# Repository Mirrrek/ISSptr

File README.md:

# ISSptr

A lil thing that points towards the ISS.

## Required hardware

- [The PCB](https://github.com/Mirrrek/ISSptr/tree/main/schematic), obviously, including:
  - [ESP32-WROOM-32-N4](https://jlcpcb.com/partdetail/EspressifSystems-ESP32_WROOM_32N4/C82899) Microcontroller
  - [QMC5883L](https://jlcpcb.com/partdetail/Qst-QMC5883L/C976032) Magnetometer
  - [ULN2003AD](https://jlcpcb.com/partdetail/TexasInstruments-ULN2003AD/C908113) Transistor Array
  - [AMS1117-3.3](https://jlcpcb.com/partdetail/Advanced_MonolithicSystems-AMS1117_33/C6186) Voltage Regulator
  - [BC817](https://jlcpcb.com/partdetail/Shikues-BC817/C475629) NPN Transistors
  - [TYPE-C-31-M-12](https://jlcpcb.com/partdetail/Korean_HropartsElec-TYPE_C_31_M12/C165948) USB-C Connector
  - [B5B-XH-A(LF)(SN)](https://jlcpcb.com/partdetail/Jst-B5B_XH_A_LF_SN/C157991) Connector
  - Some 0603 resistors and capacitors
- A servo motor (e.g. _SG90_)
- An unipolar stepper motor (e.g. _28BYJ-48_)
- 6-Channel slip ring

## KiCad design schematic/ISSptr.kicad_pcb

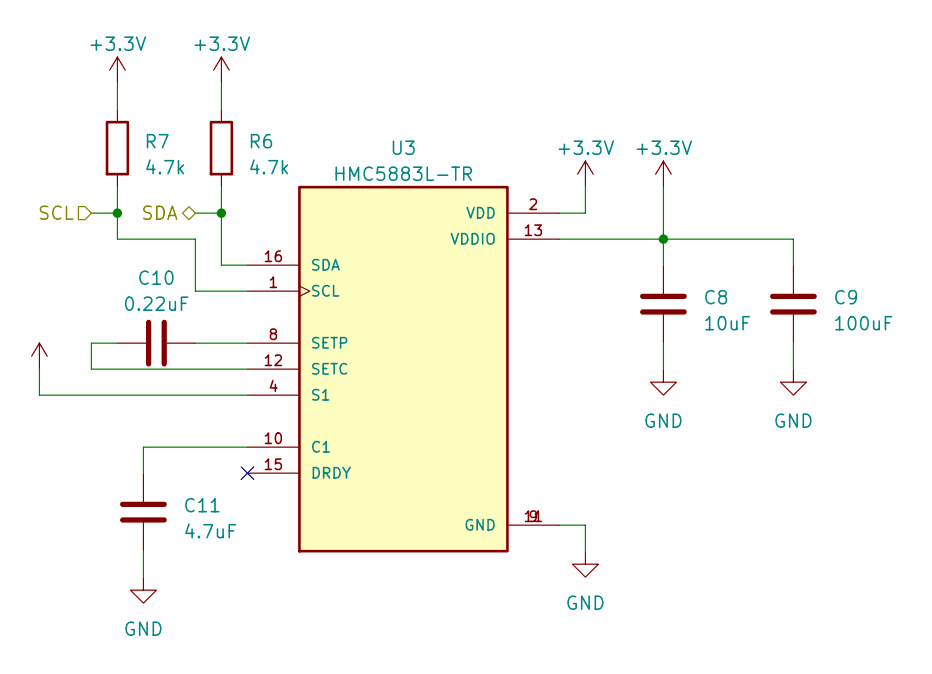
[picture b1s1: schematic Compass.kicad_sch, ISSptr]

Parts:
C8: 10uF; C_0603_1608Metric; LCSC C19702
C9: 100uF; C_0603_1608Metric; LCSC C730416
C10: 0.22uF; C_0603_1608Metric; LCSC C472764
C11: 4.7uF; C_0603_1608Metric; LCSC C307469
R6, R7: 4.7k; R_0603_1608Metric; LCSC C23162
U3: HMC5883L-TR; XDCR_HMC5883L-TR; PARTREV E; LCSC C976032

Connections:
+3.3V: C8.1, C9.1, R6.1, R7.1, U3.2 (VDD), U3.4 (S1), U3.13 (VDDIO); also elsewhere on the board
/Compass/SCL: R7.2, U3.1 (SCL); also elsewhere on the board
/Compass/SDA: R6.2, U3.16 (SDA); also elsewhere on the board
GND: C8.2, C9.2, C11.1, U3.9 (GND), U3.11 (GND); also elsewhere on the board
unnamed: C11.2, U3.10 (C1)
unnamed: C10.1, U3.12 (SETC)
unnamed: C10.2, U3.8 (SETP)

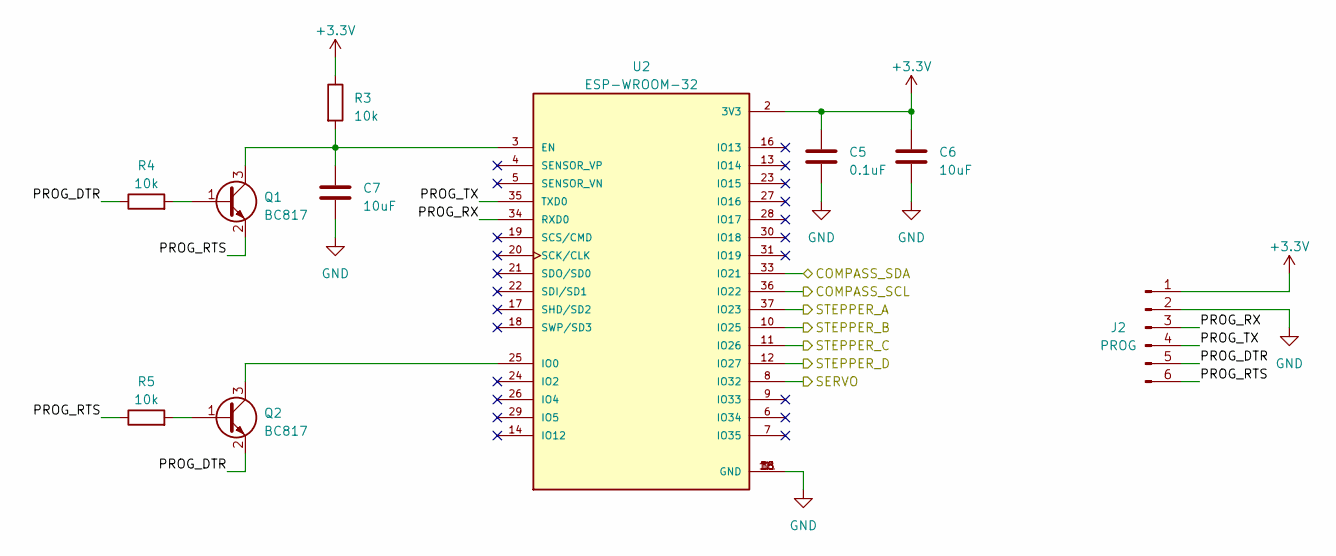
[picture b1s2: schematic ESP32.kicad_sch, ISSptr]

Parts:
C5: 0.1uF; C_0603_1608Metric; LCSC C1591
C6, C7: 10uF; C_0603_1608Metric; LCSC C19702
J2: PROG; PinHeader_1x06_P2.54mm_Vertical
Q1, Q2: BC817; SOT-23; LCSC C475629
R3, R4, R5: 10k; R_0603_1608Metric; LCSC C25804
U2: ESP-WROOM-32; MODULE_ESP-WROOM-32; LCSC C82899

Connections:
+3.3V: C5.1, C6.1, J2.1, R3.1, U2.2 (3V3); also elsewhere on the board
/Compass/SCL: U2.36 (IO22); also elsewhere on the board
/Compass/SDA: U2.33 (IO21); also elsewhere on the board
/ESP32/PROG_DTR: J2.5, Q2.2 (E), R4.1
/ESP32/PROG_RTS: J2.6, Q1.2 (E), R5.1
/ESP32/PROG_RX: J2.3, U2.34 (RXD0)
/ESP32/PROG_TX: J2.4, U2.35 (TXD0)
/ESP32/SERVO: U2.8 (IO32); also elsewhere on the board
/ESP32/STEPPER_A: U2.37 (IO23); also elsewhere on the board
/ESP32/STEPPER_B: U2.10 (IO25); also elsewhere on the board
/ESP32/STEPPER_C: U2.11 (IO26); also elsewhere on the board
/ESP32/STEPPER_D: U2.12 (IO27); also elsewhere on the board
GND: C5.2, C6.2, C7.2, J2.2, U2.1 (GND), U2.1.1 (GND), U2.15 (GND), U2.38 (GND); also elsewhere on the board
unnamed: Q1.1 (B), R4.2
unnamed: C7.1, Q1.3 (C), R3.2, U2.3 (EN)
unnamed: Q2.1 (B), R5.2
unnamed: Q2.3 (C), U2.25 (IO0)

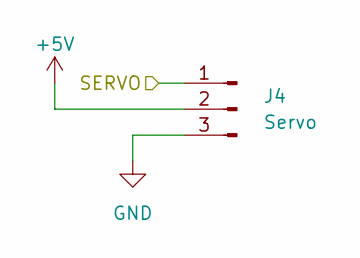
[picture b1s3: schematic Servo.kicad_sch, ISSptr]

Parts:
J4: Servo; PinHeader_1x03_P2.54mm_Horizontal

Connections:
+5V: J4.2; also elsewhere on the board
/ESP32/SERVO: J4.1; also elsewhere on the board
GND: J4.3; also elsewhere on the board

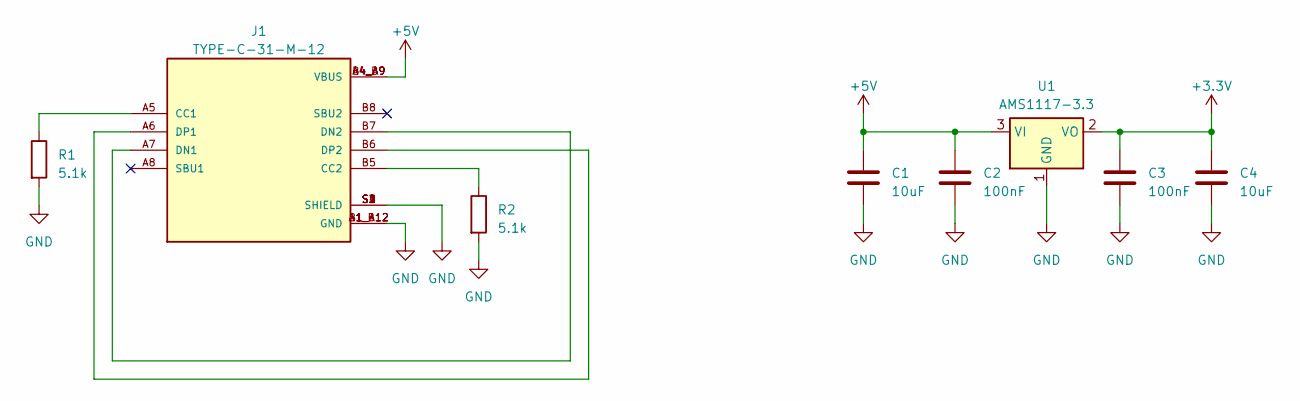
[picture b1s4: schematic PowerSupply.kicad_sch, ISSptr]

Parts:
C1, C4: 10uF; C_0603_1608Metric; LCSC C19702
C2, C3: 100nF; C_0603_1608Metric; LCSC C1591
J1: TYPE-C-31-M-12; HRO_TYPE-C-31-M-12; PARTREV 2020.12.08; LCSC C165948
R1, R2: 5.1k; R_0603_1608Metric; LCSC C23186
U1: AMS1117-3.3; SOT-223-3_TabPin2; LCSC C6186

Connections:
+3.3V: C3.1, C4.1, U1.2 (VO); also elsewhere on the board
+5V: C1.1, C2.1, J1.A4_B9 (VBUS), J1.B4_A9 (VBUS), U1.3 (VI); also elsewhere on the board
GND: C1.2, C2.2, C3.2, C4.2, J1.A1_B12 (GND), J1.B1_A12 (GND), J1.S1 (SHIELD), J1.S2 (SHIELD), J1.S3 (SHIELD), J1.S4 (SHIELD), R1.2, R2.2, U1.1 (GND); also elsewhere on the board
unnamed: J1.A5 (CC1), R1.1
unnamed: J1.B5 (CC2), R2.1
unnamed: J1.A7 (DN1), J1.B7 (DN2)
unnamed: J1.A6 (DP1), J1.B6 (DP2)

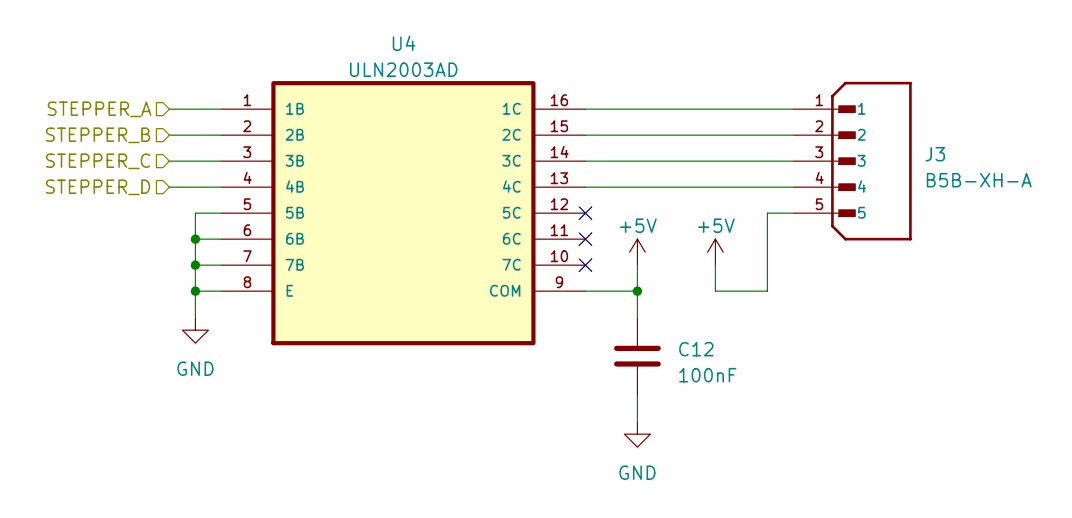
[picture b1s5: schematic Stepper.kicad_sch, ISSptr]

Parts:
C12: 100nF; C_0603_1608Metric; LCSC C1591
J3: B5B-XH-A; JST_B5B-XH-A_LF__SN_; PARTREV 7/4/21; LCSC C157991
U4: ULN2003AD; SOIC127P600X175-16N; LCSC C908113

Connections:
+5V: C12.1, J3.5, U4.9 (COM); also elsewhere on the board
/ESP32/STEPPER_A: U4.1 (1B); also elsewhere on the board
/ESP32/STEPPER_B: U4.2 (2B); also elsewhere on the board
/ESP32/STEPPER_C: U4.3 (3B); also elsewhere on the board
/ESP32/STEPPER_D: U4.4 (4B); also elsewhere on the board
GND: C12.2, U4.5 (5B), U4.6 (6B), U4.7 (7B), U4.8 (E); also elsewhere on the board
unnamed: J3.1, U4.16 (1C)
unnamed: J3.2, U4.15 (2C)
unnamed: J3.3, U4.14 (3C)
unnamed: J3.4, U4.13 (4C)

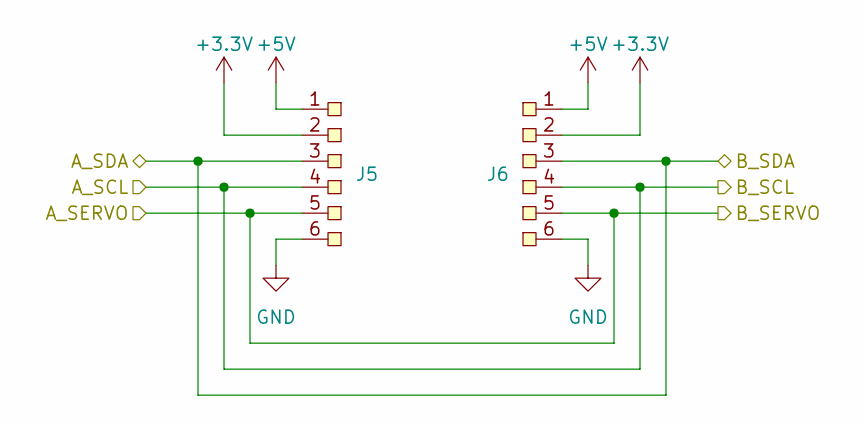
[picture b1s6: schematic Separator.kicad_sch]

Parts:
J5, J6: SolderPad-6pin

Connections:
+3.3V: J5.2, J6.2; also elsewhere on the board
+5V: J5.1, J6.1; also elsewhere on the board
/Compass/SCL: J5.4, J6.4; also elsewhere on the board
/Compass/SDA: J5.3, J6.3; also elsewhere on the board
/ESP32/SERVO: J5.5, J6.5; also elsewhere on the board
GND: J5.6, J6.6; also elsewhere on the board

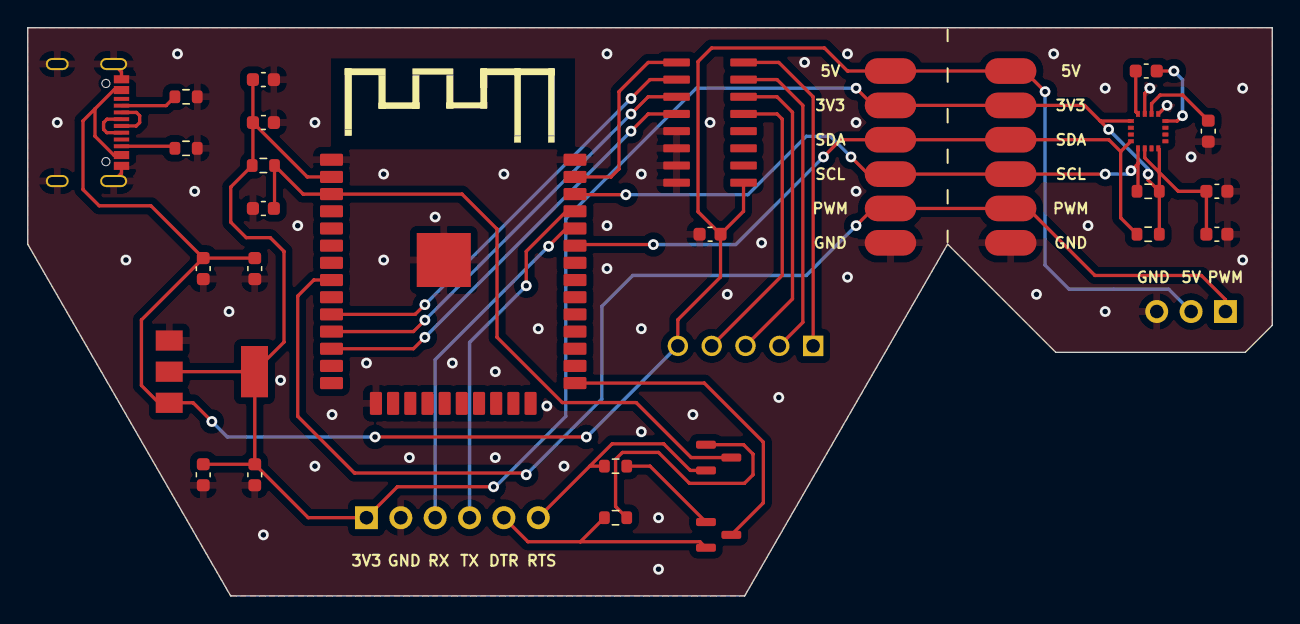
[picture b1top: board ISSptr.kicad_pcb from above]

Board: 2 copper layers, 92.0 x 42.0 mm, 31 parts (0 on the bottom side), 29 nets.

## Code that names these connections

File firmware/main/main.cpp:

#include "compass.hpp"
#include "stepper.hpp"
#include "servo.hpp"
#include "vector.hpp"
#include <freertos/FreeRTOS.h>
#include <freertos/task.h>
#include <esp_log.h>
#include <cmath>
#include <ctime>

#define PIN_COMPASS_SDA GPIO_NUM_21                 /* Compass SDA Pin */
#define PIN_COMPASS_SCL GPIO_NUM_22                 /* Compass SCL Pin */

#define PIN_STEPPER_A GPIO_NUM_16                   /* Stepper Coil 1 Terminal 1 Signal Pin */
#define PIN_STEPPER_B GPIO_NUM_17                   /* Stepper Coil 1 Terminal 2 Signal Pin */
#define PIN_STEPPER_C GPIO_NUM_18                   /* Stepper Coil 2 Terminal 1 Signal Pin */
#define PIN_STEPPER_D GPIO_NUM_19                   /* Stepper Coil 2 Terminal 2 Signal Pin */

#define PIN_SERVO GPIO_NUM_23                       /* Servo Signal Pin */

#define STEPPER_STEPS_PER_REVOLUTION 2048           /* Number of steps per full revolution of stepper */

#define COMPASS_MAX_FIELD_STRENGTH 0.5f             /* Maximum magnetic field strength considered natural (no interference) */
#define COMPASS_MAX_Z 0.25f                         /* Maximum z component of compass vector considered flat */

#define ISS_POSITION_FETCH_INTERVAL 24 * 60 * 60    /* Interval (s) of ISS position re-fetch from API */

#define COORDINATES_LAT 0.0f                        /* Latitude of user */
#define COORDINATES_LON 0.0f                        /* Longitude of user */

static const char* TAG = "main";

Vector3 latLongToVector3(float lat, float lon);
Vector3 project(Vector3 vector, Vector3 normal);
float angle(Vector3 a, Vector3 b);

extern "C" void app_main() {
    ESP_LOGI(TAG, "Initializing...");

    Compass compass(PIN_COMPASS_SDA, PIN_COMPASS_SCL);
    Stepper stepper(PIN_STEPPER_A, PIN_STEPPER_B, PIN_STEPPER_C, PIN_STEPPER_D);
    Servo servo(PIN_SERVO, true);

    Vector3 userPosition = latLongToVector3(COORDINATES_LAT, COORDINATES_LON);
    Vector3 northPoleProjected = project(Vector3(0.0f, 0.0f, 1.0f), userPosition);

    time_t lastIssPositionFetch = 0;

    ESP_LOGI(TAG, "Starting...");

    while (true) {
        ESP_LOGD(TAG, "Updating...");

        time_t currentTime = time(nullptr);
        if (currentTime - lastIssPositionFetch > ISS_POSITION_FETCH_INTERVAL) {
            ESP_LOGI(TAG, "Fetching ISS position...");

            // TODO: Fetch ISS position from API

            lastIssPositionFetch = currentTime;
        }

        Vector3 issPosition = latLongToVector3(0.0f /* TODO: Set ISS latitude */, 0.0f /* TODO: Set ISS longitude */);
        Vector3 issDirectionProjected = project(issPosition - userPosition, userPosition);

        Vector3 compassVector = compass.read();

        if (compassVector.length() > COMPASS_MAX_FIELD_STRENGTH) {
            ESP_LOGW(TAG, "Magnetic field strength too high");
            vTaskDelay(pdMS_TO_TICKS(1000));
            continue;
        }

        if (abs(compassVector.z) > COMPASS_MAX_Z) {
            ESP_LOGW(TAG, "Compass not flat");
            vTaskDelay(pdMS_TO_TICKS(1000));
            continue;
        }

        float compassAngle = angle(Vector3(compassVector.x, compassVector.y, 0.0f), Vector3(1.0f, 0.0f, 0.0f));

        float issAngle = angle(userPosition, issPosition);
        servo.set(issAngle);

        float northPoleToIssAngle = angle(northPoleProjected, issDirectionProjected);
        stepper.move((compassAngle + northPoleToIssAngle) / 360.0f * STEPPER_STEPS_PER_REVOLUTION);
    }
}

Vector3 latLongToVector3(float lat, float lon) {
    float latRad = lat / 180.0f * M_PI;
    float lonRad = lon / 180.0f * M_PI;

    return Vector3(cos(latRad) * cos(lonRad), cos(latRad) * sin(lonRad), sin(latRad));
}

Vector3 project(Vector3 vector, Vector3 normal) {
    return vector - normal * vector.dot(normal);
}

float angle(Vector3 a, Vector3 b) {
    return acos(a.dot(b) / (a.length() * b.length())) / M_PI * 180.0f;
}

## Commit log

2024-07-07 Initialize development environment
2024-07-07 Add vector library
2024-07-07 Add servo library
2024-07-07 Add stepper library
2024-07-07 Add compass library
2024-07-07 Fix compass library code
2024-07-07 Sketch out main code
2024-07-07 Create schematic layout
2024-07-08 Create power supply schematic
2024-07-08 Create ESP32 schematic
2024-07-08 Change compass library code to QMC5883
2024-07-08 Create separator schematic
2024-07-08 Create compass schematic
2024-07-08 Create servo header schematic
2024-07-08 Create stepper driver schematic
2024-07-08 Assign footprints
2024-07-08 Lay out PCB
2024-07-08 Remove component outlines on silkscreen
2024-07-08 Trace PCB
2024-07-08 Setup PCB for production
2024-08-17 Reduce PCB footprint
2024-08-17 Route PCB
